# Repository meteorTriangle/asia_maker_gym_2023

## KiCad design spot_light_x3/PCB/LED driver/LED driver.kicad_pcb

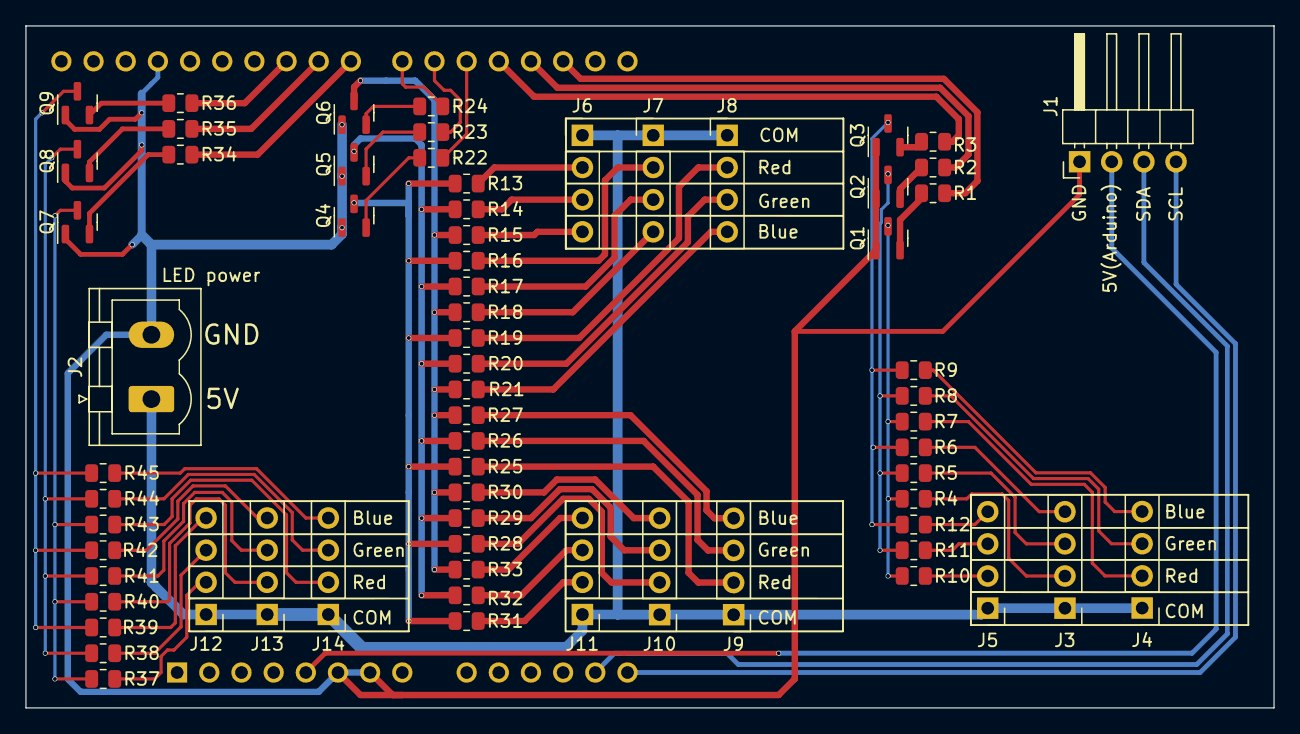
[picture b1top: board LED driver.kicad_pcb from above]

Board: 2 copper layers, 98.6 x 53.8 mm, 69 parts (1 on the bottom side), 68 nets.

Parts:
A1: Arduino_UNO_R3
J1: Conn_01x04; PinHeader_1x04_P2.54mm_Horizontal
J2: Conn_01x02; PhoenixContact_MSTBVA_2,5_2-G-5,08_1x02_P5.08mm_Vertical
J3, J4, J5, J6, J7, J8, J9, J10, J11, J12, J13, J14: Conn_01x04; PinHeader_1x04_P2.54mm_Vertical
Q1, Q2, Q3, Q4, Q5, Q6, Q7, Q8, Q9: S8050; SOT-23
R1, R2, R3, R4, R5, R6, R7, R8, R9, R10, R11, R12, R13, R14, R15, R16, R17, R18, R19, R20, R21, R22, R23, R24, R25, R26, R27, R28, R29, R30, R31, R32, R33, R34, R35, R36, R37, R38, R39, R40, R41, R42, R43, R44, R45: R; R_0805_2012Metric

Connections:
+5V: J2.1, J3.1, J4.1, J5.1, J6.1, J7.1, J8.1, J9.1, J10.1, J11.1, J12.1, J13.1, J14.1
+5VD: A1.5 (+5V), J1.2
B1: Q3.3 (C), R6.1, R9.1, R12.1
B2: Q6.3 (C), R15.1, R18.1, R21.1, R27.1, R30.1, R33.1
B3: Q9.3 (C), R39.1, R42.1, R45.1
D2: A1.17 (D2), R1.1
D3: A1.18 (D3), R2.1
D4: A1.19 (D4), R3.1
D5: A1.20 (D5), R22.1
D6: A1.21 (D6), R23.1
D7: A1.22 (D7), R24.1
D8: A1.23 (D8), R34.1
D9: A1.24 (D9), R35.1
D10: A1.25 (D10), R36.1
G1: Q2.3 (C), R5.1, R8.1, R11.1
G2: Q5.3 (C), R14.1, R17.1, R20.1, R26.1, R29.1, R32.1
G3: Q8.3 (C), R38.1, R41.1, R44.1
GND: A1.6 (GND), A1.7 (GND), A1.29 (GND), J1.1, J2.2, Q1.1 (E), Q2.1 (E), Q3.1 (E), Q4.1 (E), Q5.1 (E), Q6.1 (E), Q7.1 (E), Q8.1 (E), Q9.1 (E)
unnamed: J3.2, R4.2
unnamed: J3.3, R5.2
unnamed: J3.4, R6.2
unnamed: J4.2, R7.2
unnamed: J4.3, R8.2
unnamed: J4.4, R9.2
unnamed: J5.2, R10.2
unnamed: J5.3, R11.2
unnamed: J5.4, R12.2
unnamed: J6.2, R13.2
unnamed: J6.3, R14.2
unnamed: J6.4, R15.2
unnamed: J7.2, R16.2
unnamed: J7.3, R17.2
unnamed: J7.4, R18.2
unnamed: J8.2, R19.2
unnamed: J8.3, R20.2
unnamed: J8.4, R21.2
unnamed: J9.2, R25.2
unnamed: J9.3, R26.2
unnamed: J9.4, R27.2
unnamed: J10.2, R28.2
unnamed: J10.3, R29.2
unnamed: J10.4, R30.2
unnamed: J11.2, R31.2
unnamed: J11.3, R32.2
unnamed: J11.4, R33.2
unnamed: J12.2, R37.2
unnamed: J12.3, R38.2
unnamed: J12.4, R39.2
unnamed: J13.2, R40.2
unnamed: J13.3, R41.2
unnamed: J13.4, R42.2
unnamed: J14.2, R43.2
unnamed: J14.3, R44.2
unnamed: J14.4, R45.2
unnamed: Q1.2 (B), R1.2
unnamed: Q2.2 (B), R2.2
unnamed: Q3.2 (B), R3.2
unnamed: Q4.2 (B), R22.2
unnamed: Q5.2 (B), R23.2
unnamed: Q6.2 (B), R24.2
unnamed: Q7.2 (B), R34.2
unnamed: Q8.2 (B), R35.2
unnamed: Q9.2 (B), R36.2
R1: Q1.3 (C), R4.1, R7.1, R10.1
R2: Q4.3 (C), R13.1, R16.1, R19.1, R25.1, R28.1, R31.1
R3: Q7.3 (C), R37.1, R40.1, R43.1
SCL: A1.14 (SCL/A5), J1.4
SDA: A1.13 (SDA/A4), J1.3

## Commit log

2023-02-21 20230221 1724
2023-02-25 20230225 1105
2023-02-25 20230225 1616
2023-02-25 20230225 1821
2023-02-28 20230223 1306 home
2023-03-04 rtrt
2023-03-06 20230306 2032laptop
2023-03-14 20230315 0019
2023-03-16 20230317-0714-desktop
2023-03-17 20230317-1646-laptop
2023-03-18 20230318-2030-laptop
2023-03-19 20230319-1937-laptop
2023-03-20 20230320-2022-laptop
2023-03-21 20230321-1006-desktop
2023-03-24 v0.1.7
2023-03-25 v0.1.9
2023-03-25 v0.2.0
2023-03-26 v0.2.1
2023-03-26 20230326-2120-mylap
2023-03-26 ignore build file
2023-03-27 spot_light_LED init
2023-03-30 ws2812_release_v0.5
2023-03-31 20230323-2242-mylaptop
2023-04-05 20230405-1208-mylaptop
2023-04-09 20230409-2136-mylaptop
2023-04-11 20230411-0941
2023-04-11 20230411-1404
2023-04-11 each spot light nano code finish v1.0
2023-04-11 20230411-2350-desktop
2023-04-12 20230412-2235
2023-04-14 platform_update
2023-04-15 20230415 1050
2023-04-15 20230415 2253
2023-04-16 20230416 1154
2023-04-16 submodule
2023-04-16 ws2812 to class
2023-04-16 rainbow flow class finish
2023-04-17 audio_wave&fix platform
2023-04-17 volume_process_half
2023-04-17 del spotlight_PCB
2023-05-07 i2c test
2023-05-11 release
2023-05-12 v1.1.6
2023-05-22 test02
2023-05-22 PC communcation
2023-05-24 manual pc software
2023-05-27 elevator OK
2023-05-28 script decode pre
2023-05-29 script preview
2023-05-30 v1.3.4-bugfix
2023-05-31 v1.3.8
